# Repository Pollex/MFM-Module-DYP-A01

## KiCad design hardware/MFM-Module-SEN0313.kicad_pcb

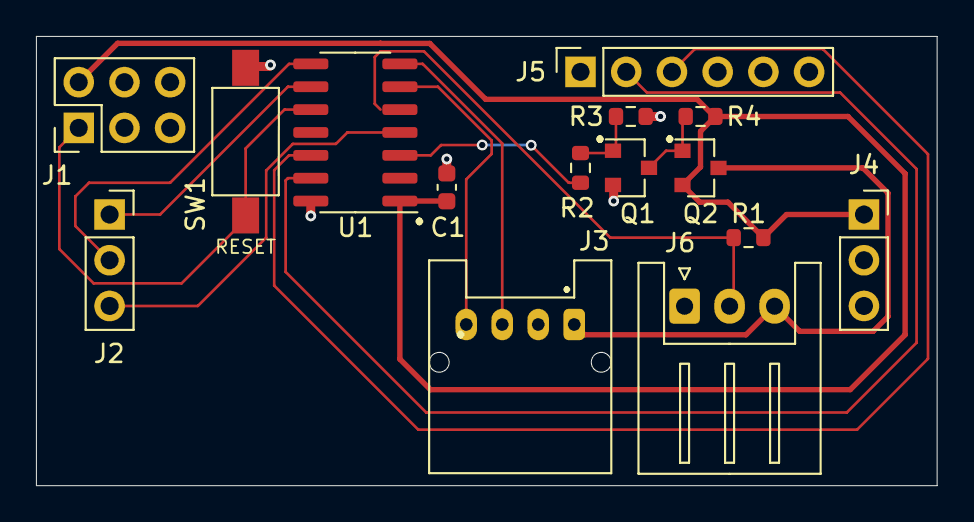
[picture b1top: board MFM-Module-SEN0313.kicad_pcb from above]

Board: 2 copper layers, 50.0 x 25.0 mm, 15 parts (0 on the bottom side), 15 nets.

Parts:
C1: 100nF; C_0603_1608Metric
J1: Program_conn; PinHeader_2x03_P2.54mm_Vertical
J2: MFM Module-Left; MFM_Module_Board_P123
J3: SEN0313 Header; JST_PA_S04B-PASK-2_1x04_P2.00mm_Horizontal
J4: MFM Module-Right; PinSocket_1x03_P2.54mm_Vertical
J5: UART Debug Connector; PinSocket_1x06_P2.54mm_Vertical
J6: DS18B20; JST_XH_S3B-XH-A_1x03_P2.50mm_Horizontal
Q1: Q_NMOS_GSD; SOT-23
Q2: Q_PMOS_GSD; SOT-23
R1: 4k7; R_0603_1608Metric
R2: 100R; R_0603_1608Metric
R3, R4: 10k; R_0603_1608Metric
SW1: PER_RESET; SW_SPST_PTS636
U1: ATtiny1614-SS; SOIC-14_3.9x8.7mm_P1.27mm

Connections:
+3V3: C1.2, J1.2, J4.1, Q2.2, R1.1, R4.1, U1.1
+3V3_SW: J3.1, J6.3, Q2.3
GND: C1.1, J1.6, J3.2, J4.3, J5.6, J6.1, Q1.2, R3.2, SW1.2, U1.14
I2C_SCL: J2.1, U1.9
I2C_SDA: J2.2, U1.8
MCU_RX: J3.4, U1.6
MCU_RX_DEBUG: J5.3, U1.12
MCU_TX: J3.3, U1.7
MCU_TX_DEBUG: J5.2, U1.13
unnamed: Q1.1, R2.1, R3.1
unnamed: Q1.3, Q2.1, R4.2
ONEWIRE: J6.2, R1.2, U1.5
RESET: J1.1, SW1.1, U1.10
SENSORS_ON: R2.2, U1.3
SMBALERT: J2.3, U1.4

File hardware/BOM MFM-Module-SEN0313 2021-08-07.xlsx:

MFM-Module-SEN0313
Quantity | Designator | Value | Footprint | Manufacturer | Manufacturer # | Note
1 | C1 | 100nF | Capacitor_SMD:C_0603_1608Metric | TDK | C1608X7R1E104K080AA | Mouser: in stock
1 | J1 | Program_conn | Connector_PinHeader_2.54mm:PinHeader_2x03_P2.54mm_Vertical | Preci-dip | 892-18-006-10-002101 | Mouser: in stock
1 | J2 | MFM Module-Left | custom_library_FP:MFM_Module_Board_P123 | Preci-dip | 801-87-003-53-001101 | Mouser: in stock
1 | J3 | SEN0313 Header | custom_library_FP:JST_PA_S04B-PASK-2_1x04_P2.00mm_Horizontal | JST (JAPAN SOLDERLESS TERMINALS) | TBD | Farnell
1 | J4 | MFM Module-Right | Connector_PinSocket_2.54mm:PinSocket_1x03_P2.54mm_Vertical | Preci-dip | 801-87-003-53-001101 | Mouser: in stock
1 | J5 | UART Debug Connector | Connector_PinSocket_2.54mm:PinSocket_1x06_P2.54mm_Vertical | Preci-dip | 801-87-006-10-001101 | Mouser: in stock
1 | J6 | DS18B20 | Connector_JST:JST_XH_S3B-XH-A_1x03_P2.50mm_Horizontal | JST (JAPAN SOLDERLESS TERMINALS) | TBD | Farnell
1 | Q1 | Q_NMOS_GSD | Package_TO_SOT_SMD:SOT-23 | Vishay | 2N7002-T1-GE3 | Mouser: in stock
1 | Q2 | Q_PMOS_GSD | Package_TO_SOT_SMD:SOT-23 | Vishay / Siliconix | SI2315BDS-T1-E3 | Mouser: in stock
1 | R1 | 4k7 | Resistor_SMD:R_0603_1608Metric | Vishay | RCC06034K70FKEA | Mouser: in stock
1 | R2 | 100R | Resistor_SMD:R_0603_1608Metric | Vishay / Dale | CRCW0603100RFKEAC | Mouser: in stock
1 | R3 | 10k | Resistor_SMD:R_0603_1608Metric | Vishay | RCC060310K0FKEA | Mouser: in stock
1 | R4 | 10k | Resistor_SMD:R_0603_1608Metric | Vishay | RCC060310K0FKEA | Mouser: in stock
1 | SW1 | PER_RESET | custom_library_FP:SW_SPST_PTS636 | C&K | PTS636 SM43 SMTR LFS | Mouser: in stock
1 | U1 | ATtiny1614-SS | Package_SO:SOIC-14_3.9x8.7mm_P1.27mm | Microchip | ATTINY1614-SSFR | Mouser: in stock

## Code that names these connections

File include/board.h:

#if !defined(_BOARD_H_)
#define _BOARD_H_

//
// PIN CONFIG
//
#define SENSOR_PWR_PORT PORTA
#define SENSOR_PWR_PIN PIN5

// PORT A
#define MCU_DBG_Port PORTA
#define MCU_RX_DBG_Pin PIN2_bp
#define MCU_TX_DBG_Pin PIN3_bp
#define SMBALERT_Port PORTA
#define SMBALERT_Pin PIN6_bp
#define ONEWIRE_Port PORTA
#define ONEWIRE_Pin PIN7_bp

// PORT B
#define I2C_Port PORTB
#define I2C_SCL_Pin PIN0_bp
#define I2C_SDA_Pin PIN1_bp

#define SEN0313_Port PORTB
#define SEN0313_TX_Pin PIN2_bp
#define SEN0313_RX_Pin PIN3_bp

#endif // _BOARD_H_

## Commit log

2021-05-06 init
2021-05-10 Update project structure add gitignore
2021-05-24 update BOM with production components. Updated PCB accordingly.
2021-10-09 ready for production (@Productronics)
2021-11-12 merge
2021-11-12 Push module-core code
2022-02-09 Remove symlinkl
2022-02-09 Add mfm-module-core submodule
2022-02-09 Chore: Update submodule
2022-02-10 Implement DS18B20 firmware, send measurement MSB
2022-02-19 Add temperature reading
2022-02-19 Use old-school data format
2022-02-26 Fix: reading module
